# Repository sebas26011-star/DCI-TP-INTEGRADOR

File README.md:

## Trabajo práctico final de la asignatura DCI ##
Este repositorio contiene el trabajo práctico final para la asignatura de Diseño de Circuitos Impresos de la carrera de posgrado de FIUBA.

* Autor: Juan Sebastian Pinto Fuentes
* Título corto del trabajo:  charger-booster module
* Descripción:  circuito cargagor y subidor de voltaje para baterias de litio 18650
* Cursada: NOV-DIC 2026

## Licencia de este trabajo ##
CERN-OHL-P-2.0
El presente proyecto se distribuye bajo la licencia CERN Open Hardware Licence Version 2.0 – Permissive (CERN-OHL-P-2.0). Esta licencia de hardware abierto permite utilizar, estudiar, fabricar, modificar y distribuir el diseño del circuito electrónico, tanto para fines académicos como comerciales, sin exigir que las modificaciones o trabajos derivados se publiquen bajo la misma licencia.
Ver archivo LICENSE.txt

## Estructura del TP FINAL ##

Se propone y se pide utilizar la siguiente estructura.

* doc: Toda la información sobre el circuito, principalmente de autoría o procesamiento propio. Por ejemplo:
  * Notas de ingeniería propias.
  * Notas de aplicación propias.
  * Estudios previos, estado del arte, resumen de las investigaciones.
  * Notas con cálculos.
  * Dibujos adicionales.
  * Fotos de los prototipos.
  * Presupuestos, cotizaciones.
* info: Toda la iformación recolectada, principalmente de terceros, como por ejemplo:
  * Hojas de datos.
  * Notas de aplicación.
  * Info de productos comerciales.
  * Info en internet.
* pcb: Archivos de diseño esquemático y pcb.

Dependiendo la magnitud del proyecto, tendremos más o menos información en estos directorios. 
Revisar los README.md en cada directorio para conocer las pautas de cada uno para este TP.

NOTA: El alumno puede y debe borrar de este archivo todo lo que considere necesario, por ejemplo las aclaraciones del docente y esta misma nota.

## Obligatorios para el TP Final ##
* doc/propuesta/README.md (con textos y links, formato markdown, a imágenes que deben estar en el mismo repo. Las imágenes son las que se piden en las pautas de TP).
* info/*.pdf (Se piden solo las hojas de datos de los componentes relevantes como circuitos integrados, conectores particulares, módulos, etc. No es necesario poner hojas de pasivos, discretos comunes, conectores estándar.)
* pcb/* (Acá va el proyecto KiCad, modelos 3D, bibliotecas particulares y archivos generados como BOM, gerbers, etc.). EVITE subir al git archivos temporales de KiCad. Se recomienda usar un .gitignore adecuado.
* El alumnos es libre de agregar otras cosas, pero siempre tenga en cuenta que el repositorio es público. Evitar colocar información personal o documentación confidencial.

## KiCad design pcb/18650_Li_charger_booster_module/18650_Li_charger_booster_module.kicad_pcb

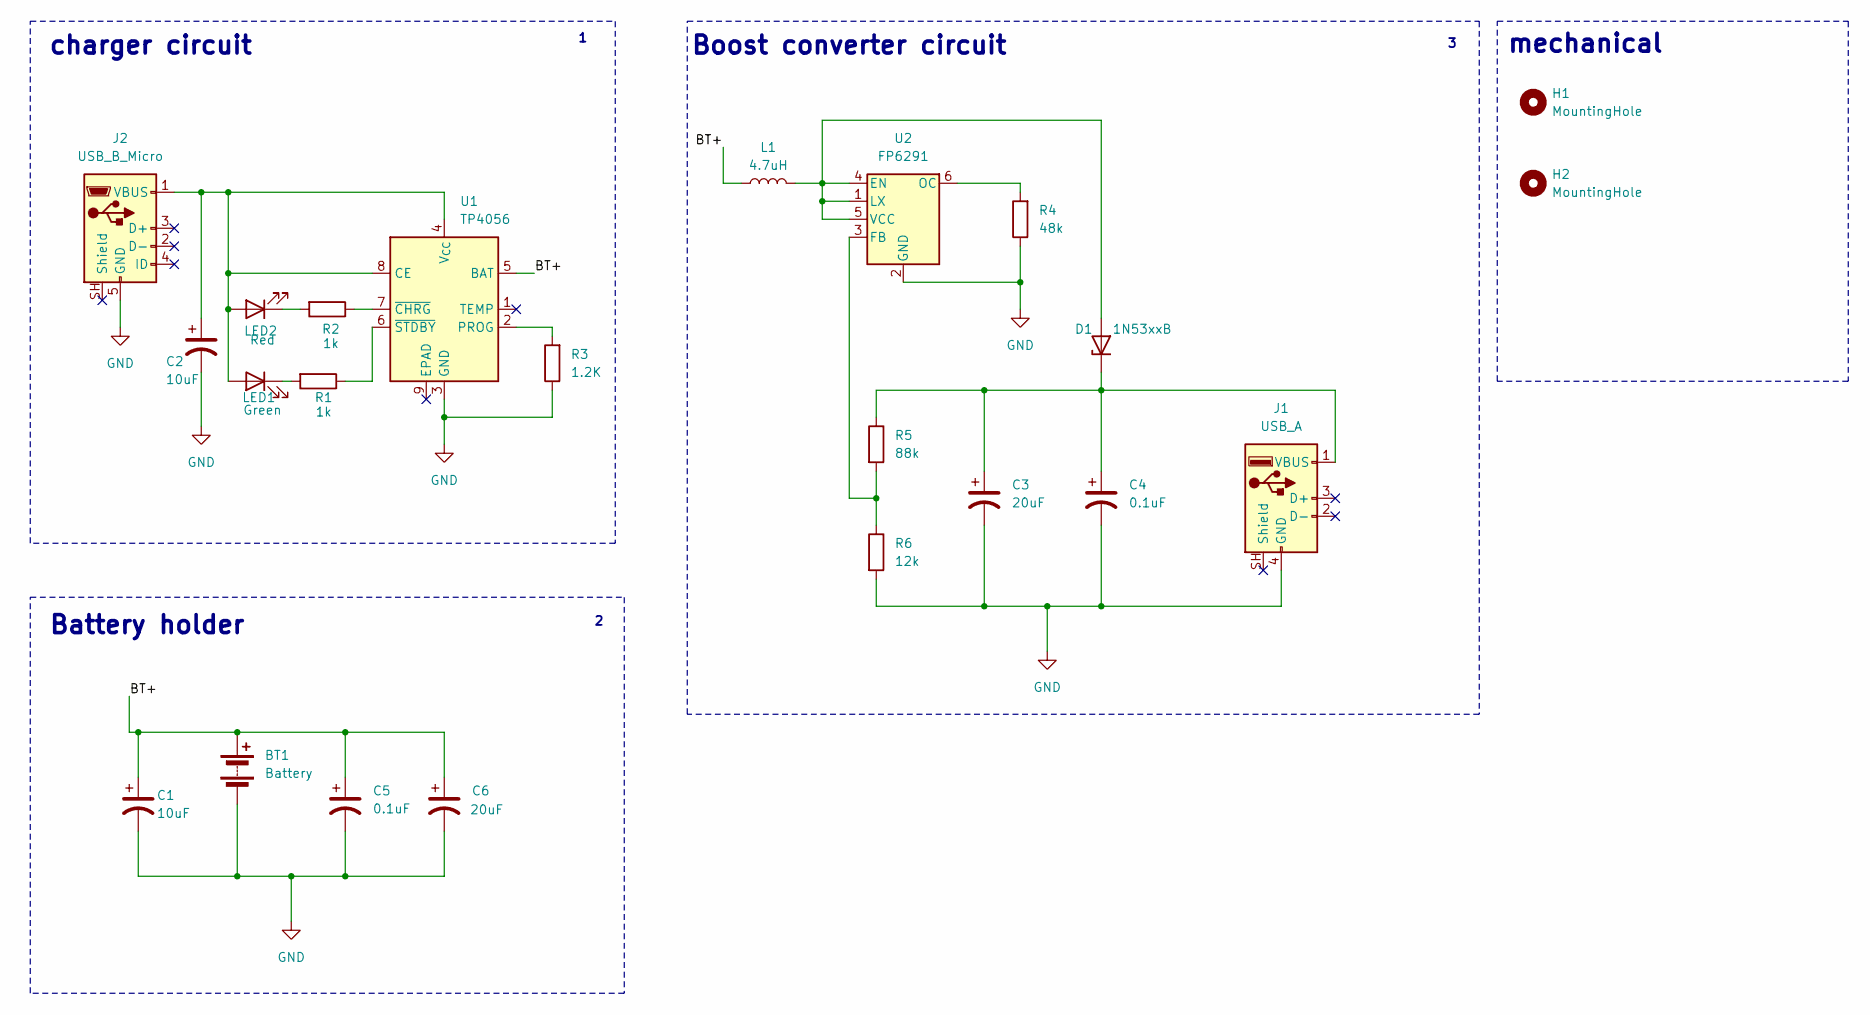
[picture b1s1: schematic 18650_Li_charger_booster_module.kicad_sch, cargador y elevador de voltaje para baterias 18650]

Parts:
BT1: Battery; BatteryHolder_Keystone_1042_1x18650
C1, C2: 10uF; CP_Radial_D5.0mm_P2.50mm
C3, C6: 20uF; CP_Radial_D5.0mm_P2.50mm
C4, C5: 0.1uF; C_Disc_D6.0mm_W2.5mm_P5.00mm
D1: 1N53xxB; D_DO-201_P15.24mm_Horizontal
H1, H2: MountingHole; MountingHole_2.2mm_M2
J1: USB_A; USB_A_Molex_67643_Horizontal
J2: USB_B_Micro; USB_Micro-B_Wuerth_629105150521
L1: 4.7uH; L_Axial_L7.0mm_D3.3mm_P10.16mm_Horizontal_Fastron_MICC
LED1: Green; LED_D8.0mm
LED2: Red; LED_D8.0mm
R1, R2: 1k; R_Axial_DIN0207_L6.3mm_D2.5mm_P7.62mm_Horizontal
R3: 1.2K; R_Axial_DIN0207_L6.3mm_D2.5mm_P7.62mm_Horizontal
R4: 48k; R_Axial_DIN0207_L6.3mm_D2.5mm_P7.62mm_Horizontal
R5: 88k; R_Axial_DIN0207_L6.3mm_D2.5mm_P7.62mm_Horizontal
R6: 12k; R_Axial_DIN0207_L6.3mm_D2.5mm_P7.62mm_Horizontal
U1: TP4056; SOIC-8-1EP_3.9x4.9mm_P1.27mm_EP2.41x3.3mm_ThermalVias
U2: FP6291; SOT-23-6

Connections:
/BT+: BT1.1 (+), C1.1, C5.1, C6.1, L1.1, U1.5 (BAT)
GND: BT1.2 (-), C1.2, C2.2, C3.2, C4.2, C5.2, C6.2, J1.4 (GND), J2.5 (GND), R3.1, R4.1, R6.2, U1.3 (GND), U2.2 (GND)
unnamed: D1.2 (A), L1.2, U2.1 (LX), U2.4 (EN), U2.5 (VCC)
unnamed: C3.1, C4.1, D1.1 (K), J1.1 (VBUS), R5.1
unnamed: C2.1, J2.1 (VBUS), LED1.2 (A), LED2.2 (A), U1.4 (V_{CC}), U1.8 (CE)
unnamed: LED1.1 (K), R1.2
unnamed: LED2.1 (K), R2.2
unnamed: R3.2, U1.2 (PROG)
unnamed: R2.1, U1.7 (~CHRG)
unnamed: R1.1, U1.6 (~STDBY)
unnamed: R5.2, R6.1, U2.3 (FB)
unnamed: R4.2, U2.6 (OC)

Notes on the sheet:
Boost converter circuit
mechanical
Battery holder
charger circuit

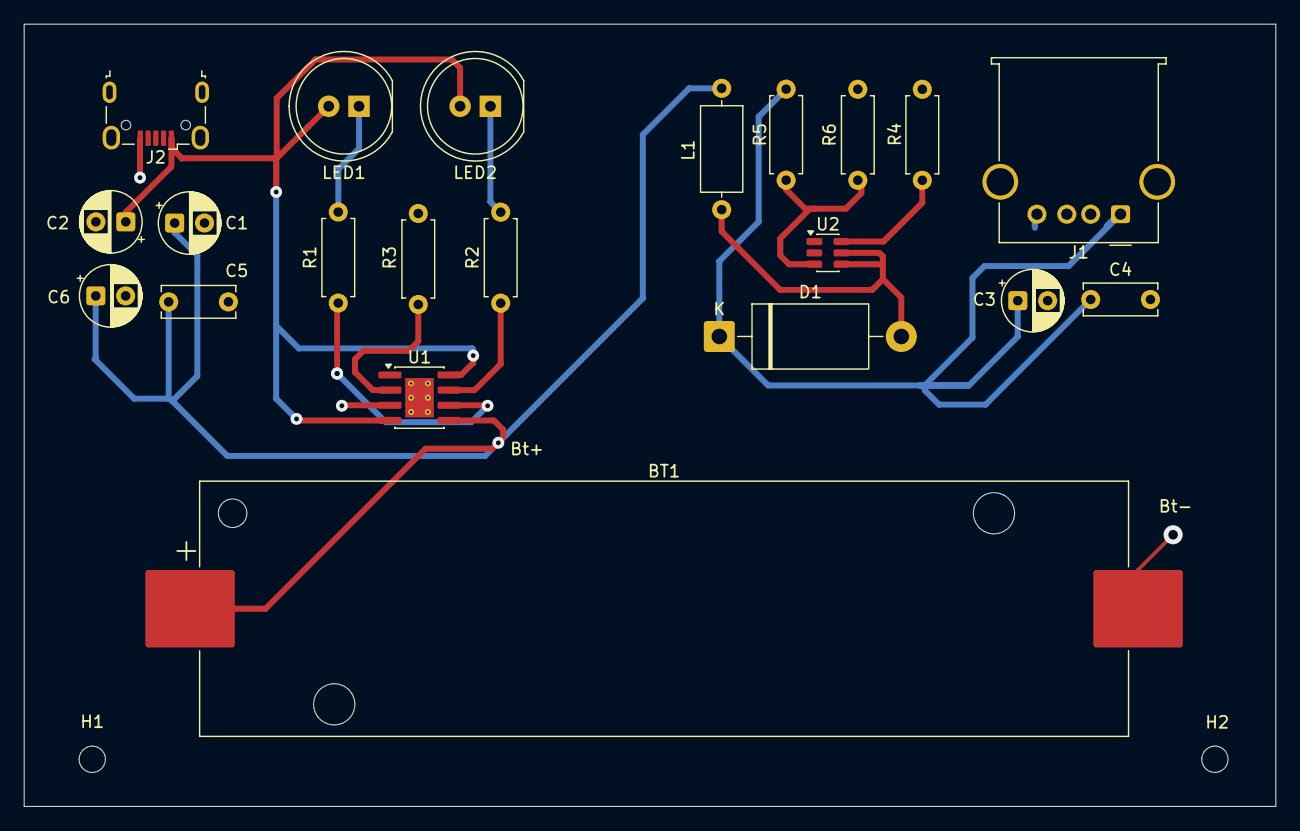
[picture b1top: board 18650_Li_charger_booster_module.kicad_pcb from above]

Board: 2 copper layers, 104.8 x 65.5 mm, 23 parts (0 on the bottom side), 12 nets.
